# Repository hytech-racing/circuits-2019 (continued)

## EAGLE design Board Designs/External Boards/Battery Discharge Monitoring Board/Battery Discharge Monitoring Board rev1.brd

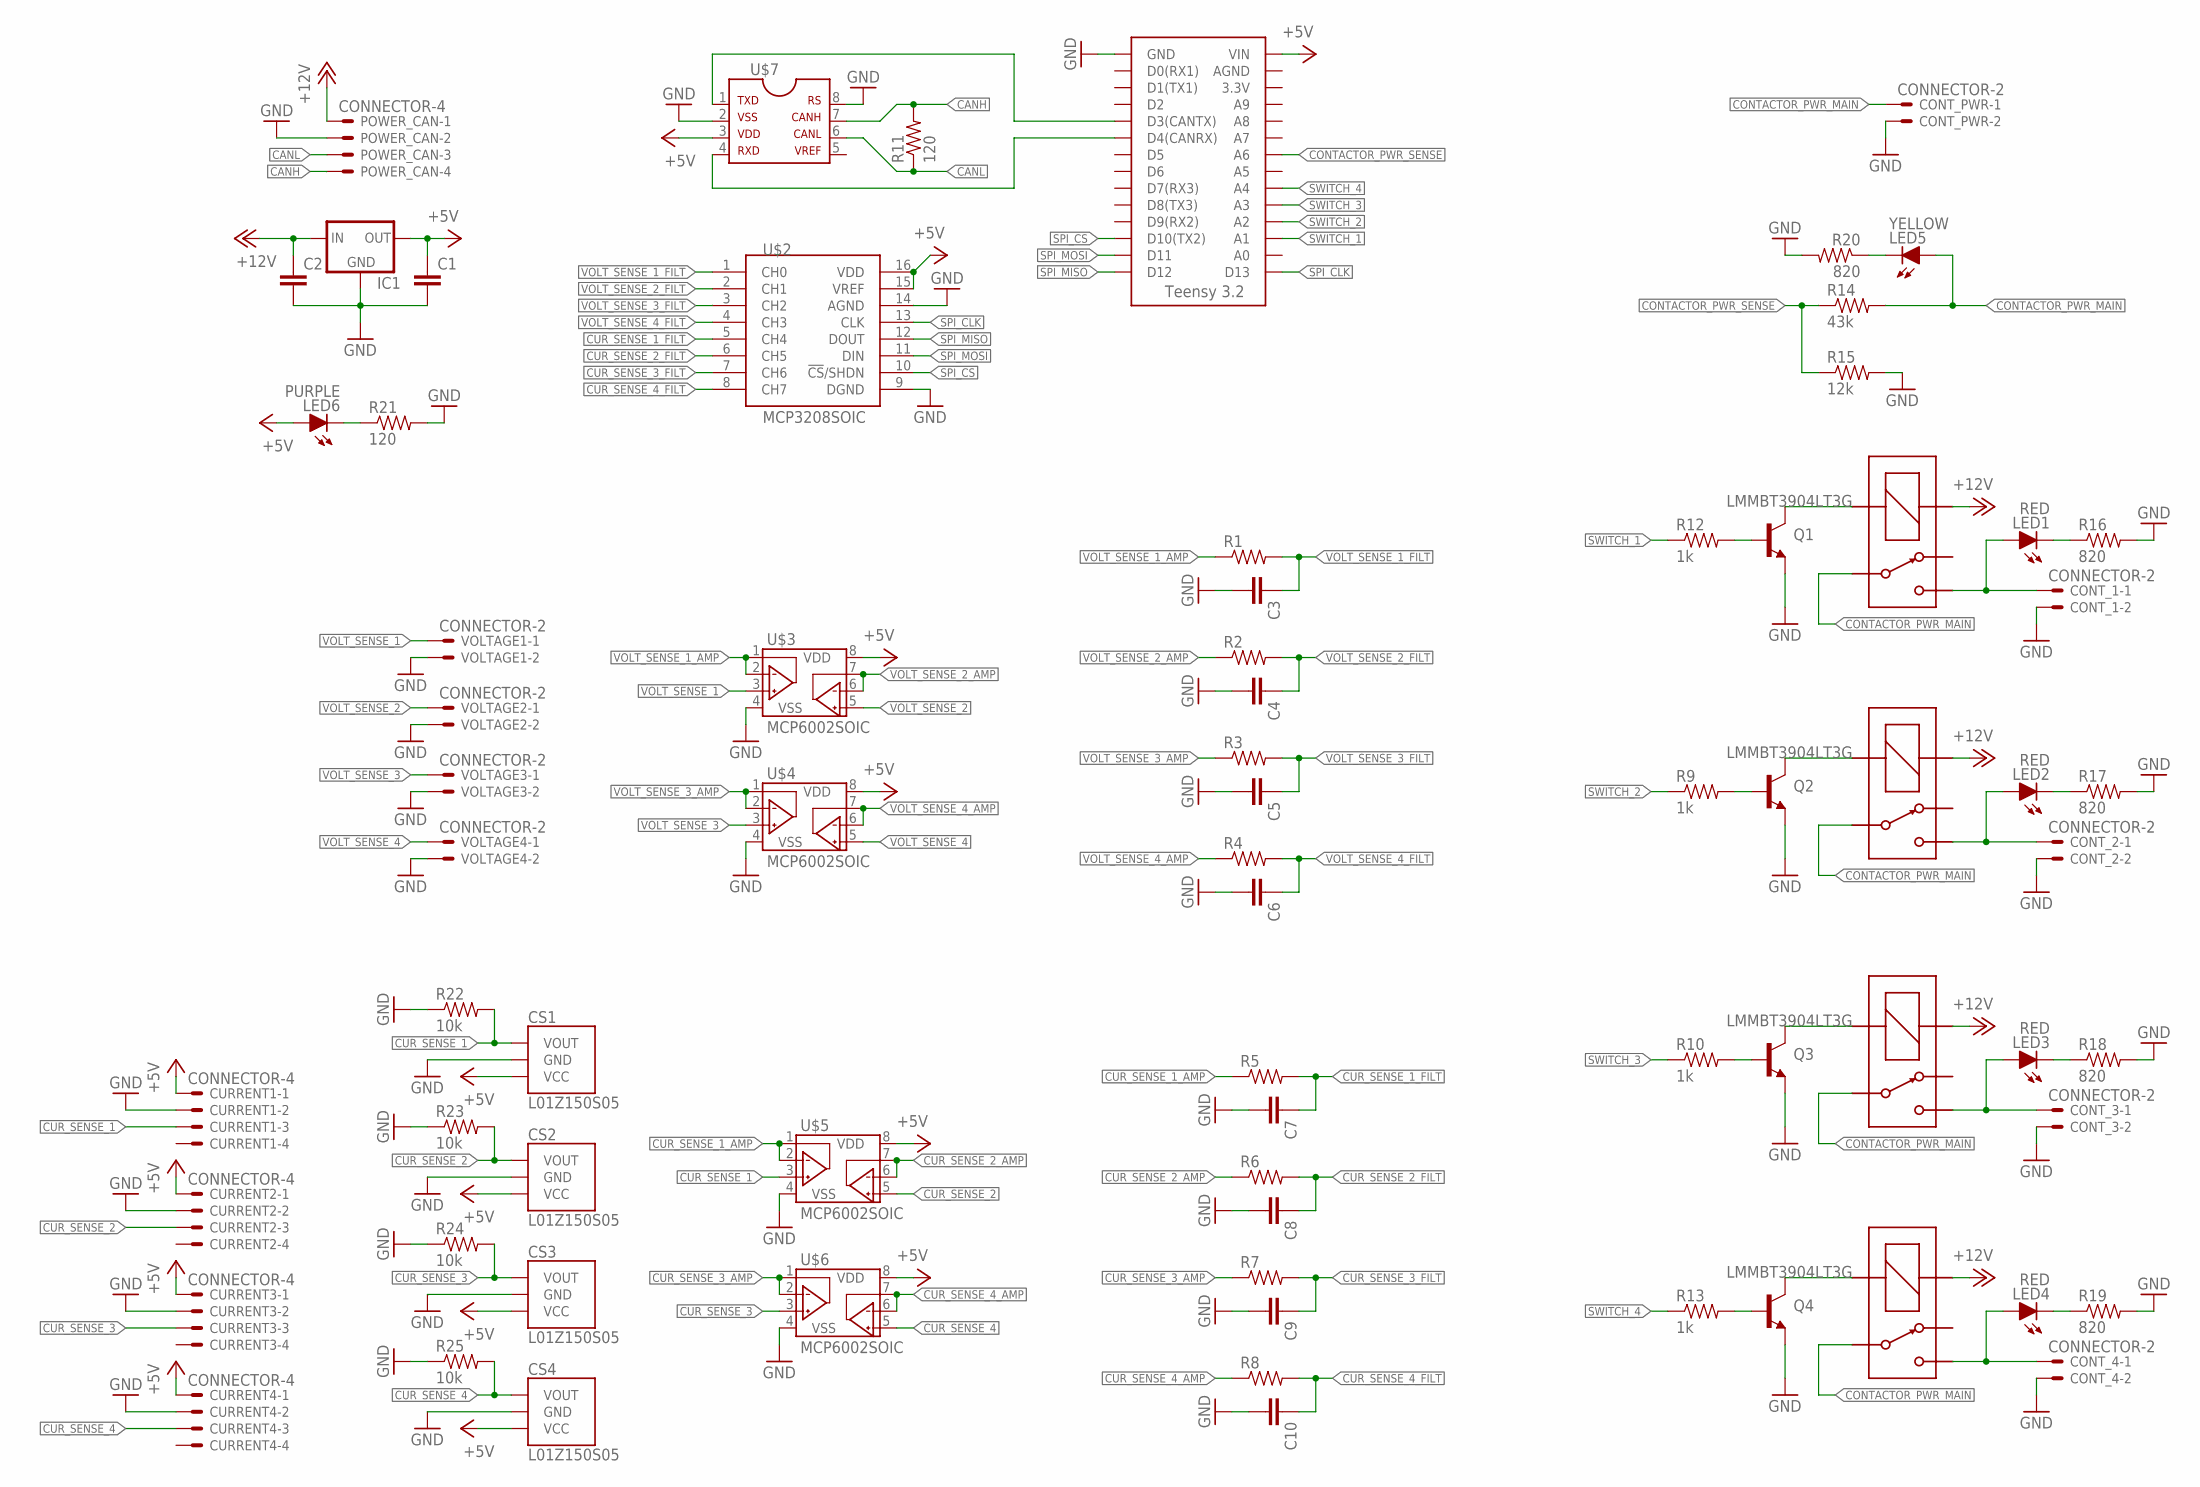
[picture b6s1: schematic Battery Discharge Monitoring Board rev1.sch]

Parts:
C1, C2, C3, C4, C5, C6, C7, C8, C9, C10: CAP0805; 0805
CONT_1, CONT_2, CONT_3, CONT_4: CONNECTOR-2; MINIFIT_5566-2
CONT_PWR: CONNECTOR-2; MINIFIT_5566-2
CS1, CS2, CS3, CS4: L01Z150S05
CURRENT1, CURRENT2, CURRENT3, CURRENT4: CONNECTOR-4; MINIFIT_5566-4
IC1: 5VREG_L7805SPACED; TO-220-SPACED
LED1, LED2, LED3, LED4: RED; LED-805
LED5: YELLOW; LED-805
LED6: PURPLE; LED-805
POWER_CAN: CONNECTOR-4; MINIFIT_5566-4
Q1, Q2, Q3, Q4: LMMBT3904LT3G; SOT23
R1, R2, R3, R4, R5, R6, R7, R8: RESISTOR0805-RES; 0805
R9, R10, R12, R13: 1k; 0805
R11, R21: 120; 0805
R14: 43k; 0805
R15: 12k; 0805
R16, R17, R18, R19, R20: 820; 0805
R22, R23, R24, R25: 10k; 0805
U$1: TEENSY_3.2_SIMPLE
U$2: MCP3208SOIC; SOIC-16
U$3, U$4, U$5, U$6: MCP6002SOIC; SOIC-08
U$7: MCP2551; SOIC-08
U$8, U$9, U$10, U$11: G5LE; ZF112
VOLTAGE1, VOLTAGE2, VOLTAGE3, VOLTAGE4: CONNECTOR-2; MINIFIT_5566-2

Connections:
+5V: C1.1, CS1.3 (VCC), CS2.3 (VCC), CS3.3 (VCC), CS4.3 (VCC), CURRENT1.1, CURRENT2.1, CURRENT3.1, CURRENT4.1, IC1.3 (OUT), LED6.A, U$1.VIN, U$2.15 (VREF), U$2.16 (VDD), U$3.8 (VDD), U$4.8 (VDD), U$5.8 (VDD), U$6.8 (VDD), U$7.3
+12V: C2.1, IC1.1 (IN), POWER_CAN.1, U$8.1 (COIL+), U$9.1 (COIL+), U$10.1 (COIL+), U$11.1 (COIL+)
CANH: POWER_CAN.4, R11.2, U$7.7
CANL: POWER_CAN.3, R11.1, U$7.6
CONTACTOR_PWR_1: CONT_1.1, LED1.A, U$8.S
CONTACTOR_PWR_2: CONT_2.1, LED2.A, U$9.S
CONTACTOR_PWR_3: CONT_3.1, LED3.A, U$10.S
CONTACTOR_PWR_4: CONT_4.1, LED4.A, U$11.S
CONTACTOR_PWR_MAIN: CONT_PWR.1, LED5.A, R14.2, U$8.P, U$9.P, U$10.P, U$11.P
CONTACTOR_PWR_SENSE: R14.1, R15.1, U$1.A6
CUR_SENSE_1: CS1.1 (VOUT), CURRENT1.3, R22.2, U$5.3 (VINA+)
CUR_SENSE_1_AMP: R5.1, U$5.1 (VOUTA), U$5.2 (VINA-)
CUR_SENSE_1_FILT: C7.1, R5.2, U$2.5 (CH4)
CUR_SENSE_2: CS2.1 (VOUT), CURRENT2.3, R23.2, U$5.5 (VINB+)
CUR_SENSE_2_AMP: R6.1, U$5.6 (VINB-), U$5.7 (VOUTB)
CUR_SENSE_2_FILT: C8.1, R6.2, U$2.6 (CH5)
CUR_SENSE_3: CS3.1 (VOUT), CURRENT3.3, R24.2, U$6.3 (VINA+)
CUR_SENSE_3_AMP: R7.1, U$6.1 (VOUTA), U$6.2 (VINA-)
CUR_SENSE_3_FILT: C9.1, R7.2, U$2.7 (CH6)
CUR_SENSE_4: CS4.1 (VOUT), CURRENT4.3, R25.2, U$6.5 (VINB+)
CUR_SENSE_4_AMP: R8.1, U$6.6 (VINB-), U$6.7 (VOUTB)
CUR_SENSE_4_FILT: C10.1, R8.2, U$2.8 (CH7)
GND: C1.2, C2.2, C3.2, C4.2, C5.2, C6.2, C7.2, C8.2, C9.2, C10.2, CONT_1.2, CONT_2.2, CONT_3.2, CONT_4.2, CONT_PWR.2, CS1.2 (GND), CS2.2 (GND), CS3.2 (GND), CS4.2 (GND), CURRENT1.2, CURRENT2.2, CURRENT3.2, CURRENT4.2, IC1.2 (GND), POWER_CAN.2, Q1.2 (EMITTER), Q2.2 (EMITTER), Q3.2 (EMITTER), Q4.2 (EMITTER), R15.2, R16.2, R17.2, R18.2, R19.2, R20.2, R21.2, R22.1, R23.1, R24.1, R25.1, U$1.GND, U$2.9 (DGND), U$2.14 (AGND), U$3.4 (VSS), U$4.4 (VSS), U$5.4 (VSS), U$6.4 (VSS), U$7.2, U$7.8, VOLTAGE1.2, VOLTAGE2.2, VOLTAGE3.2, VOLTAGE4.2
unnamed: U$1.D3(CANTX), U$7.1
unnamed: U$1.D4(CANRX), U$7.4
unnamed: Q2.1 (BASE), R9.2
unnamed: Q1.1 (BASE), R12.2
unnamed: Q1.3 (COLLECTOR), U$8.2 (COIL-)
unnamed: Q2.3 (COLLECTOR), U$9.2 (COIL-)
unnamed: Q3.1 (BASE), R10.2
unnamed: Q3.3 (COLLECTOR), U$10.2 (COIL-)
unnamed: Q4.1 (BASE), R13.2
unnamed: Q4.3 (COLLECTOR), U$11.2 (COIL-)
unnamed: LED2.C, R17.1
unnamed: LED1.C, R16.1
unnamed: LED3.C, R18.1
unnamed: LED4.C, R19.1
unnamed: LED5.C, R20.1
unnamed: LED6.C, R21.1
SPI_CLK: U$1.D13, U$2.13 (CLK)
SPI_CS: U$1.D10(TX2), U$2.10 (!CS!/SHDN)
SPI_MISO: U$1.D12, U$2.12 (DOUT)
SPI_MOSI: U$1.D11, U$2.11 (DIN)
SWITCH_1: R12.1, U$1.A1
SWITCH_2: R9.1, U$1.A2
SWITCH_3: R10.1, U$1.A3
SWITCH_4: R13.1, U$1.A4
VOLT_SENSE_1: U$3.3 (VINA+), VOLTAGE1.1
VOLT_SENSE_1_AMP: R1.1, U$3.1 (VOUTA), U$3.2 (VINA-)
VOLT_SENSE_1_FILT: C3.1, R1.2, U$2.1 (CH0)
VOLT_SENSE_2: U$3.5 (VINB+), VOLTAGE2.1
VOLT_SENSE_2_AMP: R2.1, U$3.6 (VINB-), U$3.7 (VOUTB)
VOLT_SENSE_2_FILT: C4.1, R2.2, U$2.2 (CH1)
VOLT_SENSE_3: U$4.3 (VINA+), VOLTAGE3.1
VOLT_SENSE_3_AMP: R3.1, U$4.1 (VOUTA), U$4.2 (VINA-)
VOLT_SENSE_3_FILT: C5.1, R3.2, U$2.3 (CH2)
VOLT_SENSE_4: U$4.5 (VINB+), VOLTAGE4.1
VOLT_SENSE_4_AMP: R4.1, U$4.6 (VINB-), U$4.7 (VOUTB)
VOLT_SENSE_4_FILT: C6.1, R4.2, U$2.4 (CH3)

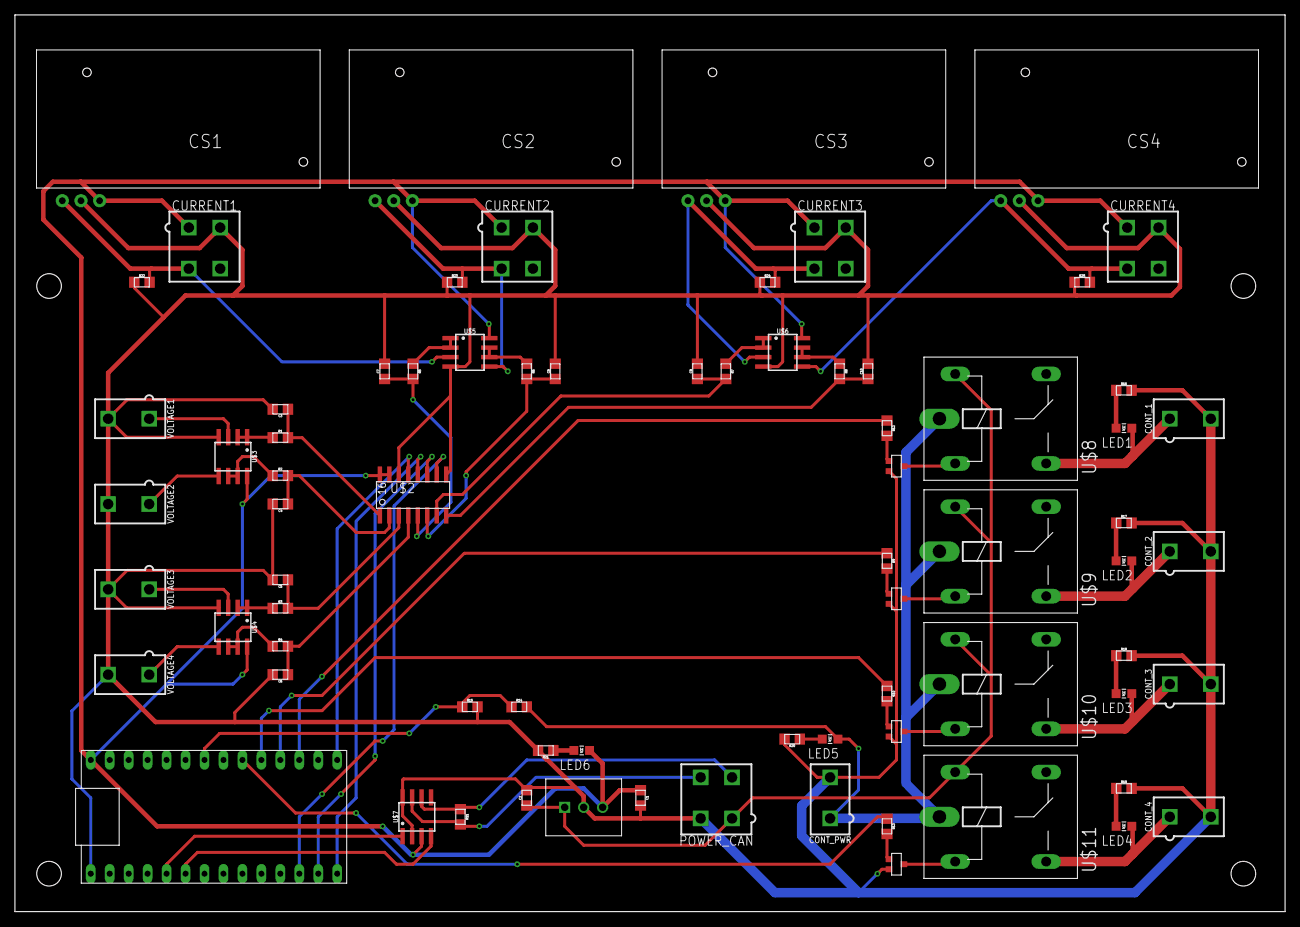
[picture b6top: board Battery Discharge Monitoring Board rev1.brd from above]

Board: 2 copper layers, 170.2 x 120.1 mm, 75 parts (0 on the bottom side), 59 nets.
